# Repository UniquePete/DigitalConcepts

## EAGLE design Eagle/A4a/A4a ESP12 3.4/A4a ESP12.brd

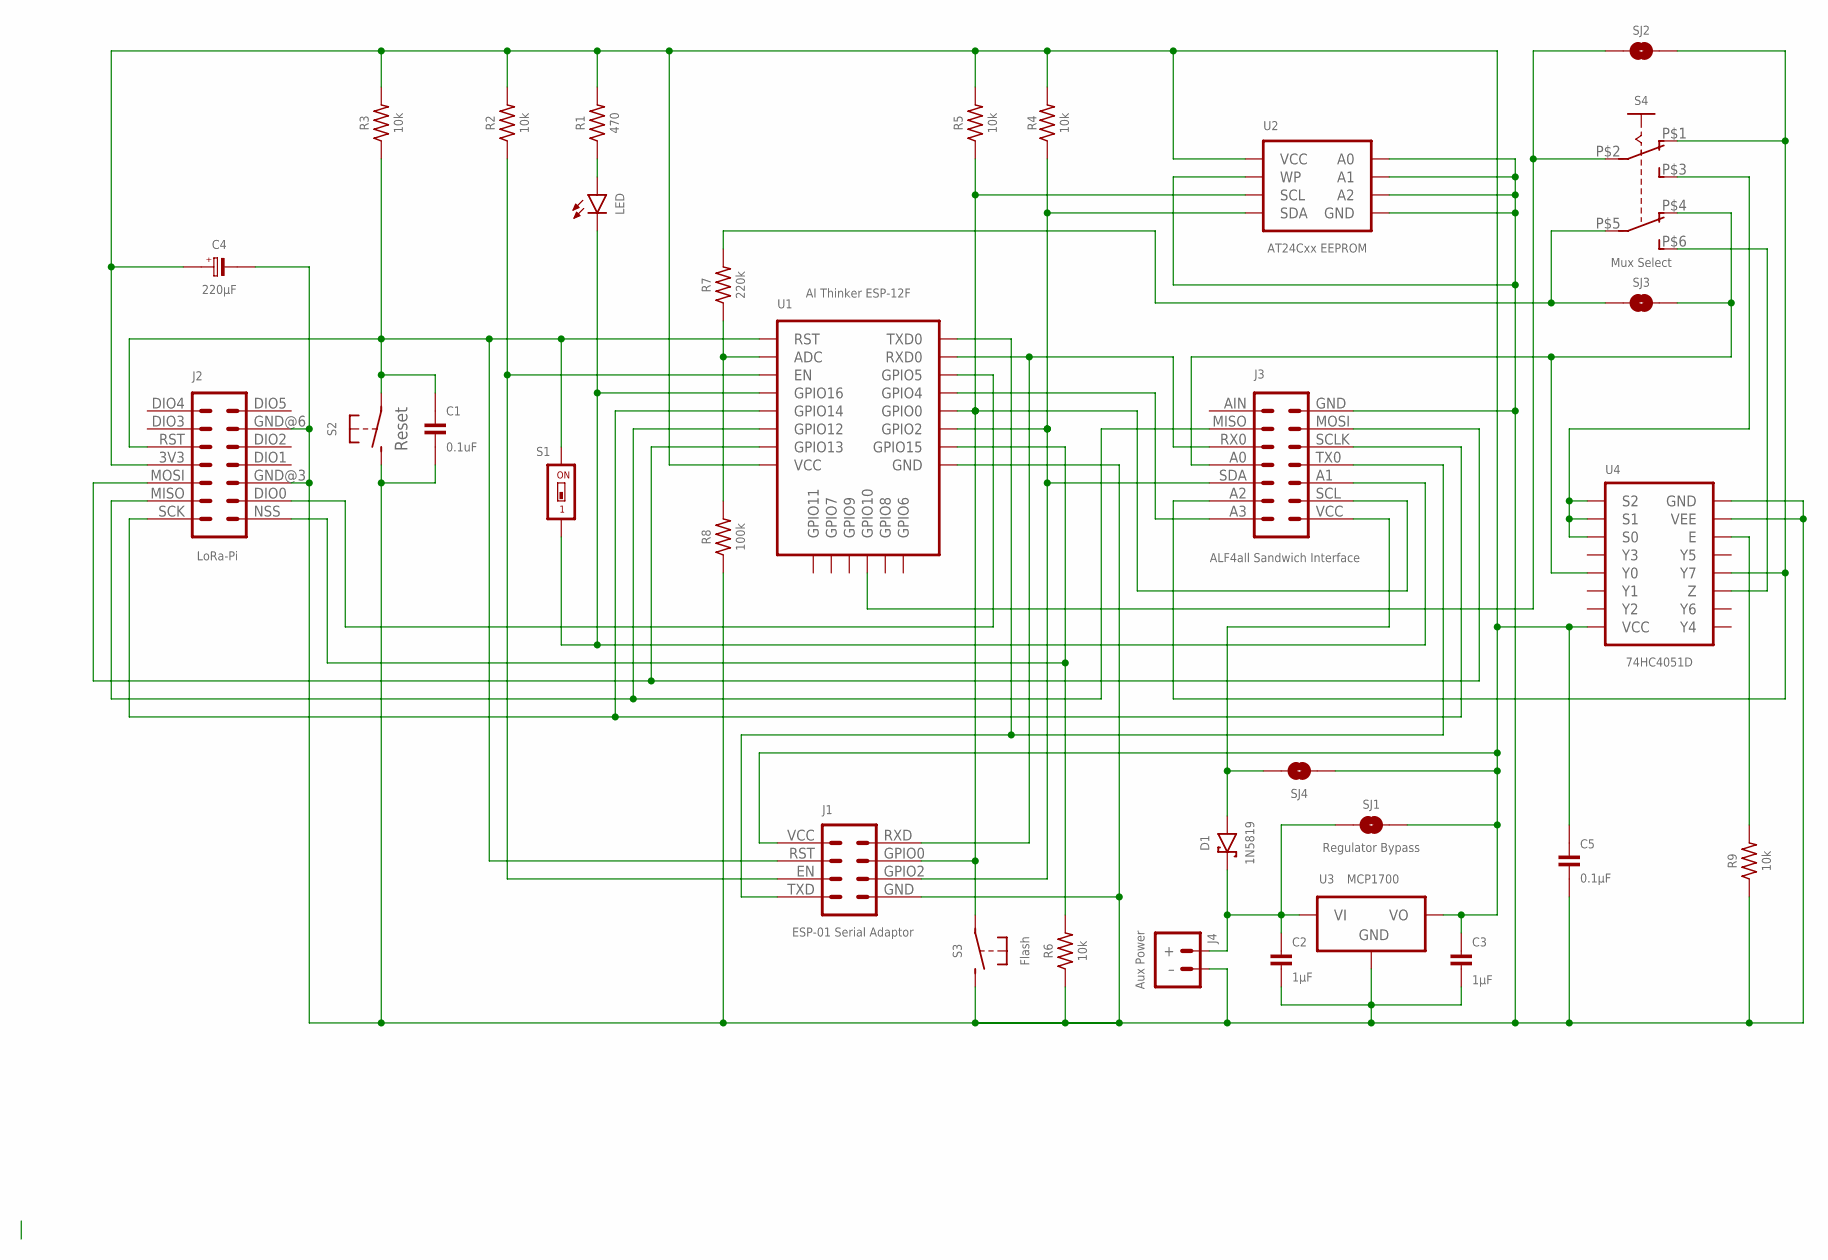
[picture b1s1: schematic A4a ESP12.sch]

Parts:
C1: 0.1uF; C0805
C2, C3: 1µF; C0805@1
C4: 220µF; C3528-21
C5: 0.1µF; C0805
D1: 1N5819; SOD-123
J1: ESP-01 Serial Adaptor; CONN_2X4-ESP-01-SERIAL
J2: LoRa-Pi; RFM95W-PI
J3: ALF4all Sandwich Interface; CONN_2X7-ALF4ALL-PROCESSOR-B
J4: Aux Power; JST-PH2.0-2-HORIZONTAL
LED: LEDCHIP-LED0805; CHIP-LED0805
R1: 470; R0805
R2, R3, R4, R5, R6, R9: 10k; R0805
R7: 220k; R0805
R8: 100k; R0805
S1: Wake; SMD-001
S2: Reset; SWITCH-2-PAD
S3: Flash; SWITCH-2-PAD
S4: Mux Select; SWITCH-DPDT-SMD
SJ1: Regulator Bypass; SJ
SJ2, SJ3, SJ4: SJ
U1: AI Thinker ESP-12F; ESP-12E/F
U2: AT24Cxx EEPROM; SOP-8
U3: MCP1700; SOT-23-3
U4: 74HC4051D; SOP16

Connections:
GND: C1.2, C2.2, C3.2, C4.2 (-), C5.2, J1.GND (1), J2.GND@3 (3), J2.GND@6 (6), J3.GND (7), J4.- (–), R6.1, R8.1, R9.1, S2.P$2 (S), S3.P$2 (S), U1.GND, U2.P$1 (A0), U2.P$2 (A1), U2.P$3 (A2), U2.P$4 (GND), U2.P$7 (WP), U3.1 (GND), U4.7 (VEE), U4.8 (GND)
unnamed: S4.P$2 (P1), SJ2.1, U1.GPIO10
unnamed: J2.NSS (1), R6.2, U1.GPIO15
unnamed: J2.SCK (14), J3.SCLK (5), U1.GPIO14
unnamed: C1.1, J1.RST (6), J2.RST (10), R3.1, S1.2, S2.P$1, U1.RST
unnamed: J2.MISO (13), J3.MISO (9), U1.GPIO12
unnamed: J2.MOSI (12), J3.MOSI (6), U1.GPIO13
unnamed: R7.1, R8.2, U1.ADC
unnamed: J1.EN (7), R2.1, U1.EN
unnamed: D1.A, J3.VCC (1), SJ4.1
unnamed: J1.TXD (8), J3.TX0 (4), U1.TXD0
unnamed: J1.GPIO2 (2), J3.SDA (12), R4.1, U1.GPIO2, U2.P$5 (SDA)
unnamed: J3.A3 (14), U1.GPIO4
unnamed: J1.GPIO0 (3), J3.SCL (2), R5.1, S3.P$1, U1.GPIO0, U2.P$6 (SCL)
unnamed: LED.A, R1.1
unnamed: J3.A1 (3), LED.C, S1.1, U1.GPIO16
unnamed: J1.RXD (4), J3.RX0 (10), U1.RXD0
unnamed: R9.2, U4.6 (E)
unnamed: J2.DIO0 (2), U1.GPIO5
unnamed: J3.A2 (13), S4.P$1 (O1), SJ2.2, U4.4 (Y7)
unnamed: J3.A0 (11), S4.P$4 (O2), SJ3.2, U4.13 (Y0)
unnamed: S4.P$6 (S2), U4.3 (Z)
unnamed: S4.P$3 (S1), U4.9 (S2), U4.10 (S1), U4.11 (S0)
unnamed: R7.2, S4.P$5 (P2), SJ3.1
unnamed: C2.1, D1.C, J4.+, SJ1.1, U3.3 (VI)
VCC: C3.1, C4.1 (+), C5.1, J1.VCC (5), J2.3V3 (11), R1.2, R2.2, R3.2, R4.2, R5.2, SJ1.2, SJ4.2, U1.VCC, U2.P$8 (VCC), U3.2 (VO), U4.16 (VCC)

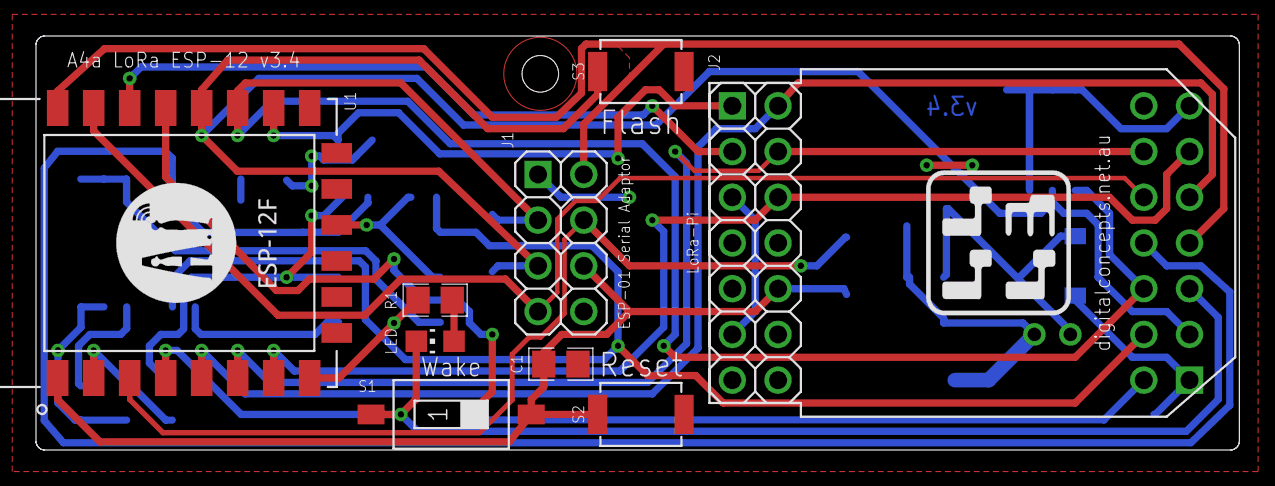
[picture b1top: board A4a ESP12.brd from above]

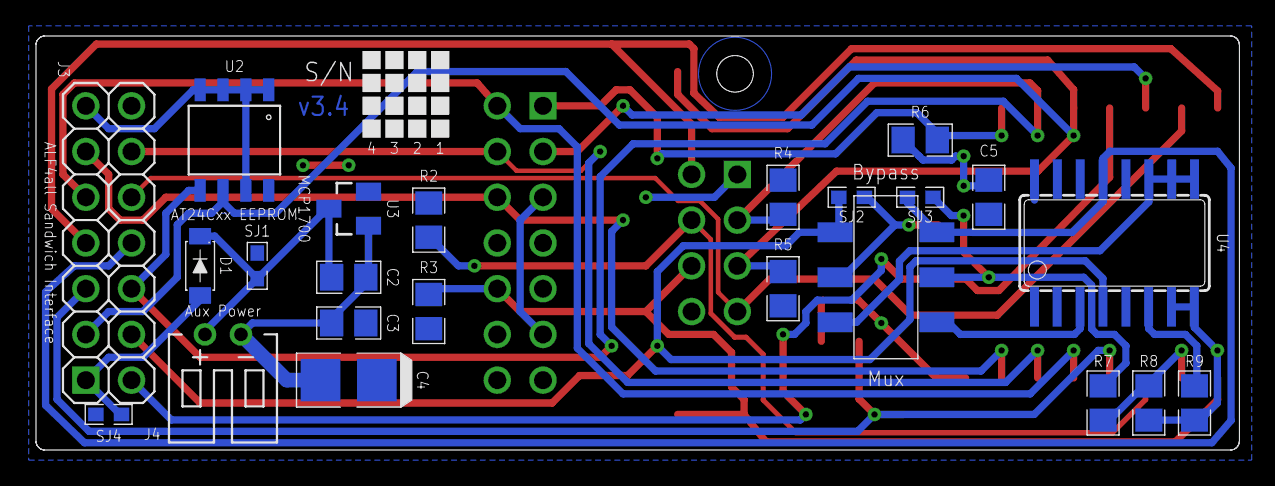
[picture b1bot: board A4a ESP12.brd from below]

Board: 2 copper layers, 66.9 x 23.0 mm, 32 parts (22 on the bottom side), 26 nets.

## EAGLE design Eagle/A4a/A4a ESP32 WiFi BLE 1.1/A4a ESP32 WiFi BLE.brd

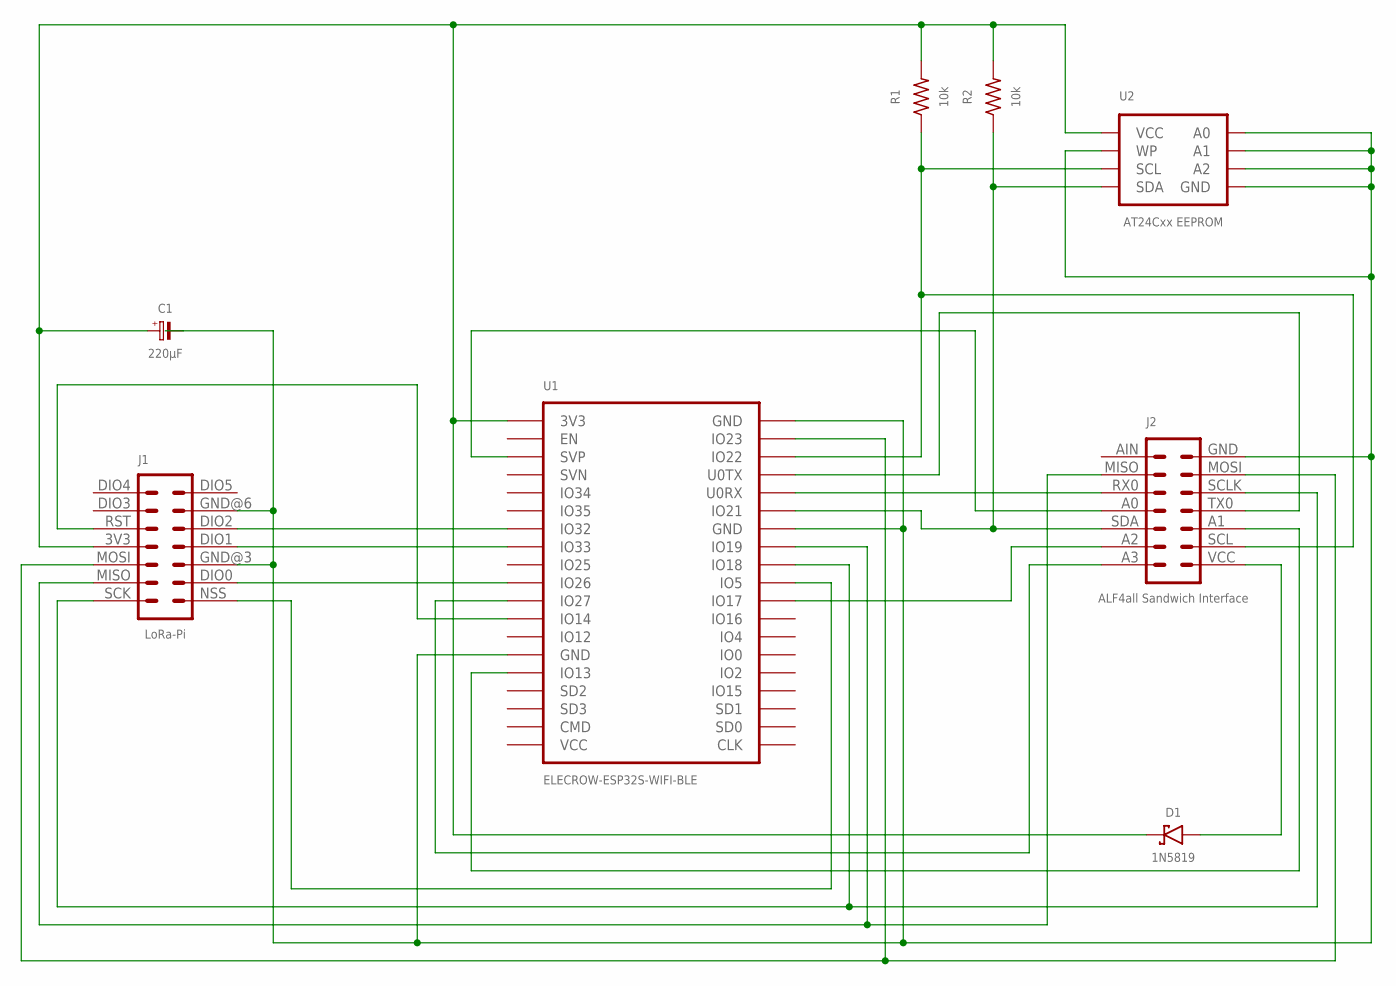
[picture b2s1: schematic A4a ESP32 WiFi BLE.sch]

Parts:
C1: 220µF; C3528-21
D1: 1N5819; SOD-123
J1: LoRa-Pi; RFM95W-PI
J2: ALF4all Sandwich Interface; CONN_2X7-ALF4ALL-PROCESSOR-B
R1, R2: 10k; R0805
U1: ELECROW-ESP32S-WIFI-BLE
U2: AT24Cxx EEPROM; SOP-8

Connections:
GND: C1.2 (-), J1.GND@3 (3), J1.GND@6 (6), J2.GND (7), U1.GND@13 (GND), U1.GND@19 (GND), U1.GND@33 (GND), U2.P$1 (A0), U2.P$2 (A1), U2.P$3 (A2), U2.P$4 (GND), U2.P$7 (WP)
unnamed: J2.A3 (14), U1.IO27
unnamed: J2.A1 (3), U1.IO13
unnamed: J1.RST (10), U1.IO14
unnamed: D1.A, J2.VCC (1)
unnamed: J1.SCK (14), J2.SCLK (5), U1.IO18
unnamed: J2.RX0 (10), U1.U0RX
unnamed: J1.DIO0 (2), U1.IO26
unnamed: J2.SDA (12), R2.1, U1.IO21, U2.P$5 (SDA)
unnamed: J2.SCL (2), R1.1, U1.IO22, U2.P$6 (SCL)
unnamed: J1.MISO (13), J2.MISO (9), U1.IO19
unnamed: J1.MOSI (12), J2.MOSI (6), U1.IO23
unnamed: J2.TX0 (4), U1.U0TX
unnamed: J1.NSS (1), U1.IO5
unnamed: J2.A2 (13), U1.IO17
unnamed: J1.DIO1 (4), U1.IO33
unnamed: J1.DIO2 (5), U1.IO32
unnamed: J2.A0 (11), U1.SVP
VCC: C1.1 (+), D1.C, J1.3V3 (11), R1.2, R2.2, U1.3V3, U2.P$8 (VCC)

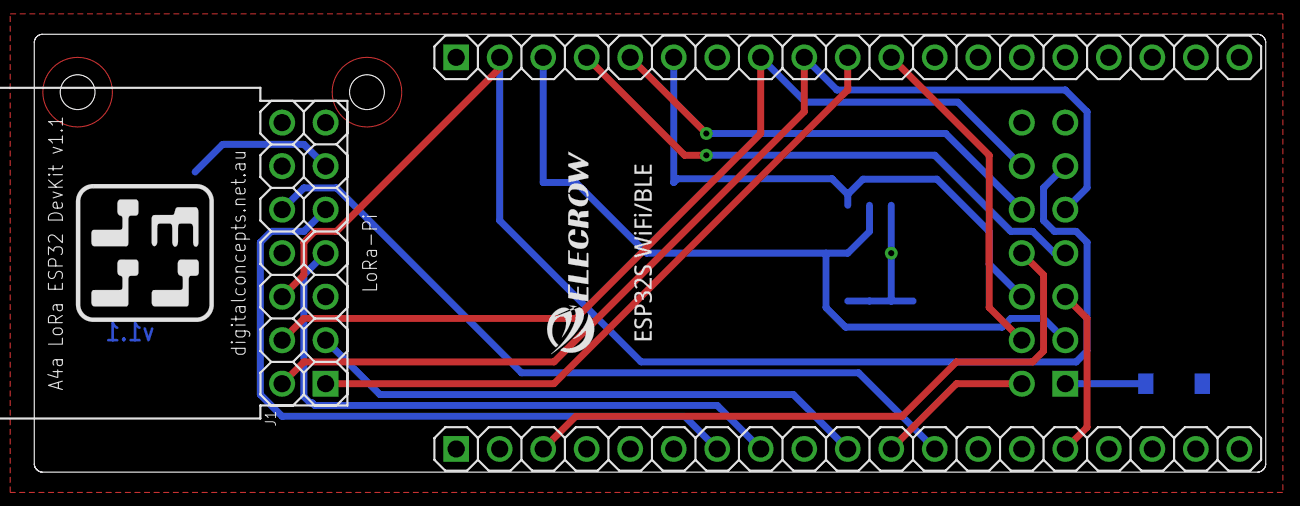
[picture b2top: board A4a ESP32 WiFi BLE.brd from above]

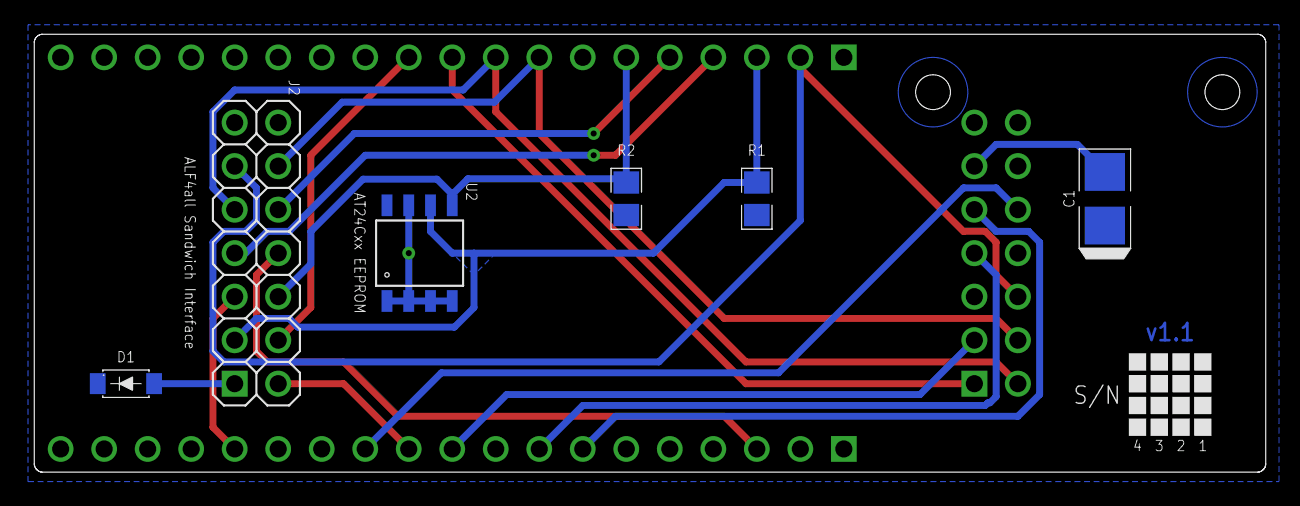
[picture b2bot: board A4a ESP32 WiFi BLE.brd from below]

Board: 2 copper layers, 71.9 x 25.6 mm, 8 parts (5 on the bottom side), 19 nets.

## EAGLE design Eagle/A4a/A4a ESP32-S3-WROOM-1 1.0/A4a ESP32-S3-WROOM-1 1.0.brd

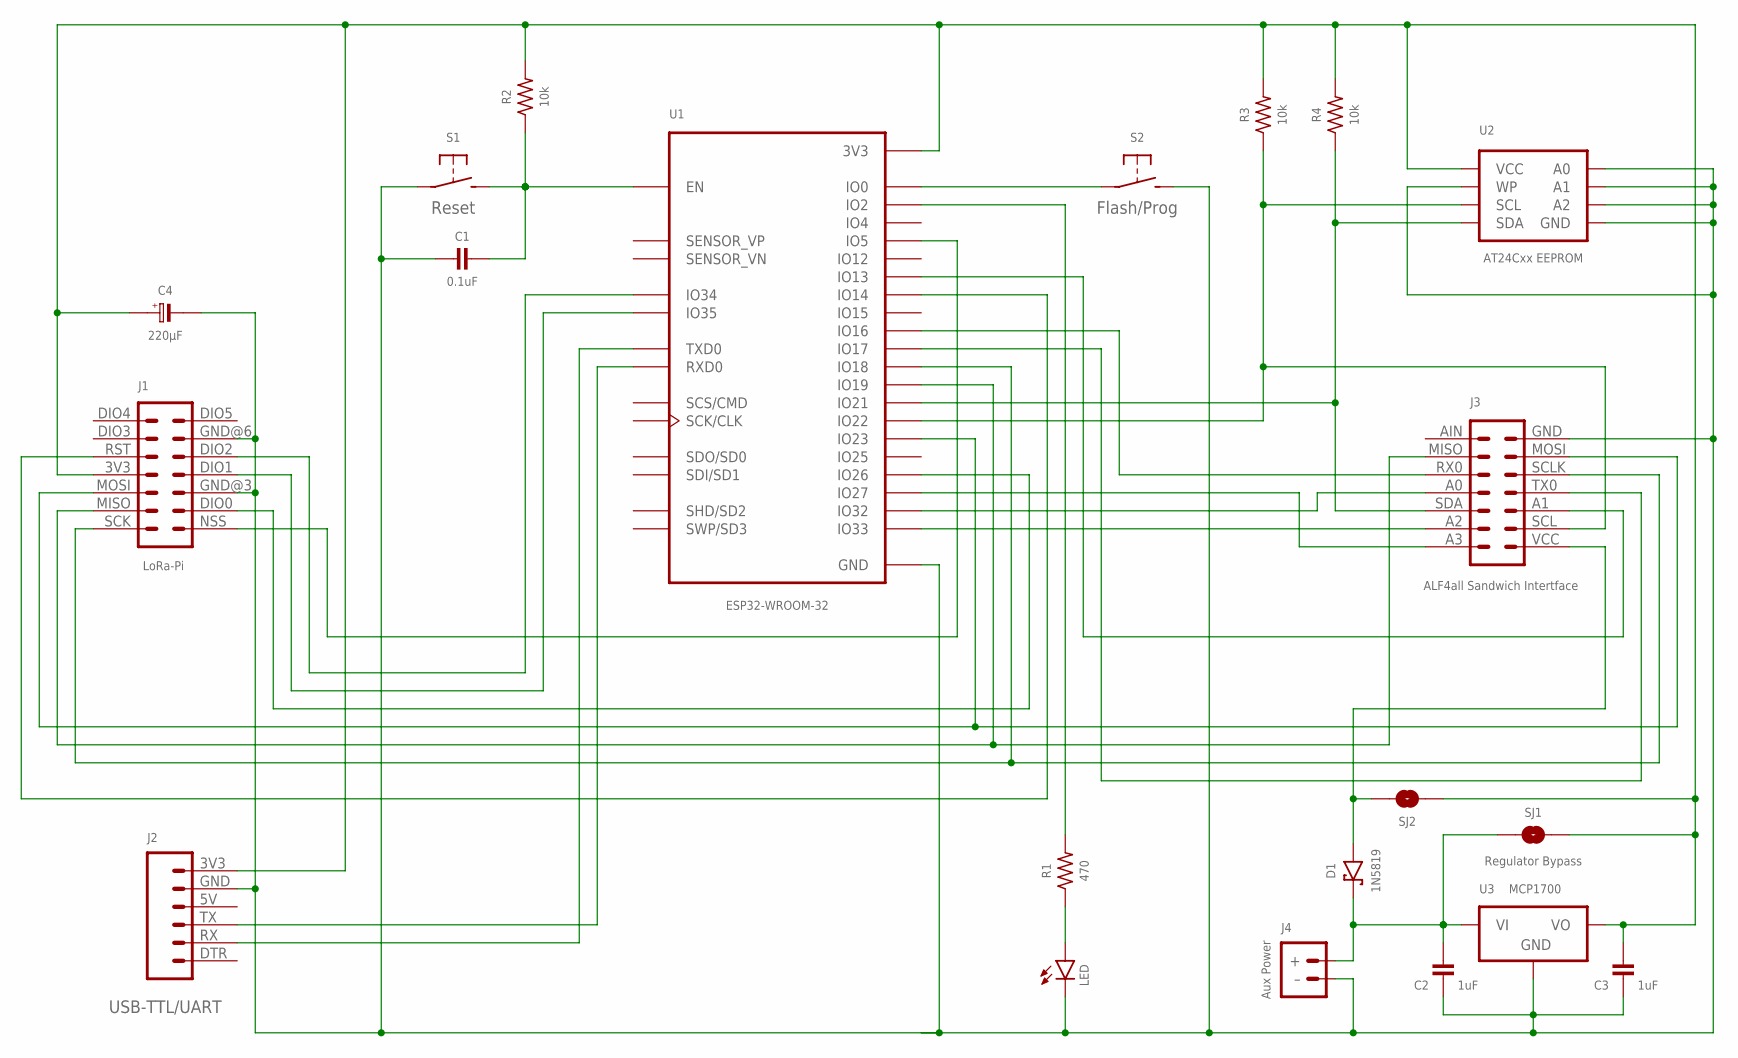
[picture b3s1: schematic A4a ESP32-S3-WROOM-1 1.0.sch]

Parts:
C1: 0.1uF; C0805@1
C2, C3: 1uF; C0805@1
C4: 220µF; C3528-21
D1: 1N5819; SOD-123
J1: LoRa-Pi; RFM95W-PI
J2: USB-TTL/UART; CONN_06-UART
J3: ALF4all Sandwich Intertface; CONN_2X7-ALF4ALL-PROCESSOR-B
J4: Aux Power; JST-PH2.0-2-HORIZONTAL
LED: LEDCHIP-LED0805; CHIP-LED0805
R1: 470; R0805
R2, R3, R4: 10k; R0805
S1: Reset; SWITCH-2-PAD
S2: Flash/Prog; SWITCH-2-PAD
SJ1: Regulator Bypass; SJ
SJ2: SJ
U1: ESP32-WROOM-32
U2: AT24Cxx EEPROM; SOP-8
U3: MCP1700; SOT-23-3

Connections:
GND: C1.2, C2.2, C3.2, C4.2 (-), J1.GND@3 (3), J1.GND@6 (6), J2.GND (5), J3.GND (7), J4.- (–), LED.C, S1.P$1, S2.P$2 (S), U1.GND@1 (GND), U1.GND@15 (GND), U1.GND@38 (GND), U1.TP (GND), U1.TP@P1 (GND), U1.TP@P2 (GND), U1.TP@P3 (GND), U1.TP@P4 (GND), U1.TP@P5 (GND), U1.TP@P6 (GND), U1.TP@P7 (GND), U1.TP@P8 (GND), U1.TP@P9 (GND), U1.TP@V1 (GND), U1.TP@V2 (GND), U1.TP@V3 (GND), U1.TP@V4 (GND), U1.TP@V5 (GND), U1.TP@V6 (GND), U1.TP@V7 (GND), U1.TP@V8 (GND), U1.TP@V9 (GND), U1.TP@V10 (GND), U1.TP@V11 (GND), U1.TP@V12 (GND), U1.TP@VP5 (GND), U2.P$1 (A0), U2.P$2 (A1), U2.P$3 (A2), U2.P$4 (GND), U2.P$7 (WP), U3.1 (GND)
unnamed: J1.DIO2 (5), U1.IO34
unnamed: J1.NSS (1), U1.IO5
unnamed: J1.SCK (14), J3.SCLK (5), U1.IO18
unnamed: J1.RST (10), U1.IO14
unnamed: J1.MISO (13), J3.MISO (9), U1.IO19
unnamed: J1.MOSI (12), J3.MOSI (6), U1.IO23
unnamed: LED.A, R1.1
unnamed: S2.P$1, U1.IO0
unnamed: J3.RX0 (10), U1.IO16
unnamed: C2.1, D1.C, J4.+, SJ1.1, U3.3 (VI)
unnamed: D1.A, J3.VCC (1), SJ2.1
unnamed: J3.SCL (2), R3.1, U1.IO22, U2.P$6 (SCL)
unnamed: C1.1, R2.1, S1.P$2 (S), U1.EN
unnamed: J3.SDA (12), R4.1, U1.IO21, U2.P$5 (SDA)
unnamed: J3.A1 (3), U1.IO13
unnamed: J2.TX (3), U1.RXD0
unnamed: R1.2, U1.IO2
unnamed: J1.DIO0 (2), U1.IO26
unnamed: J3.A2 (13), U1.IO33
unnamed: J2.RX (2), U1.TXD0
unnamed: J3.A0 (11), U1.IO32
unnamed: J3.A3 (14), U1.IO27
unnamed: J1.DIO1 (4), U1.IO35
VC: J3.TX0 (4), U1.IO17
VCC: C3.1, C4.1 (+), J1.3V3 (11), J2.3V3 (6), R2.2, R3.2, R4.2, SJ1.2, SJ2.2, U1.3V3, U2.P$8 (VCC), U3.2 (VO)

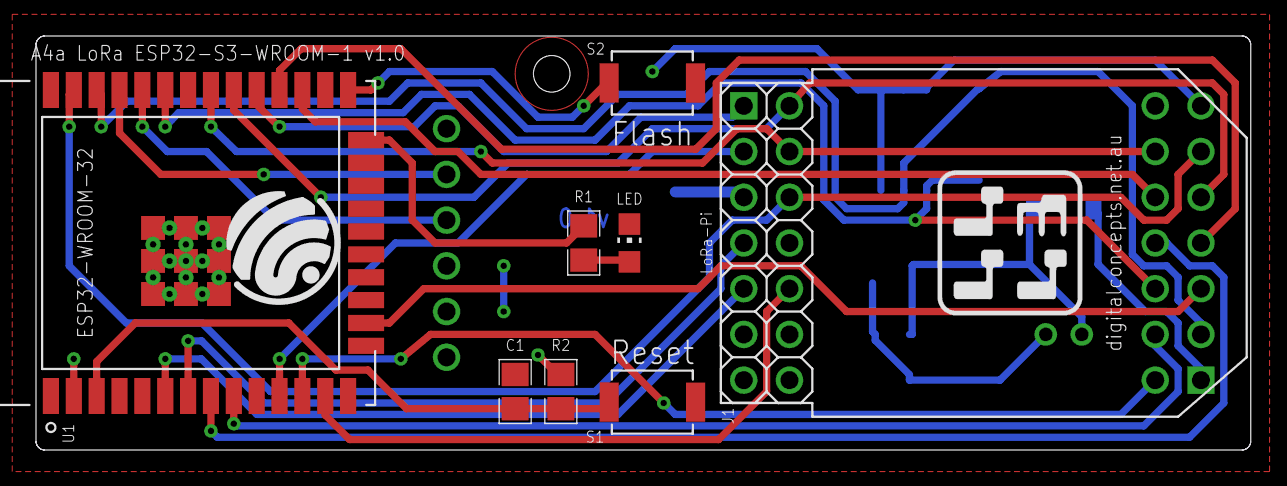
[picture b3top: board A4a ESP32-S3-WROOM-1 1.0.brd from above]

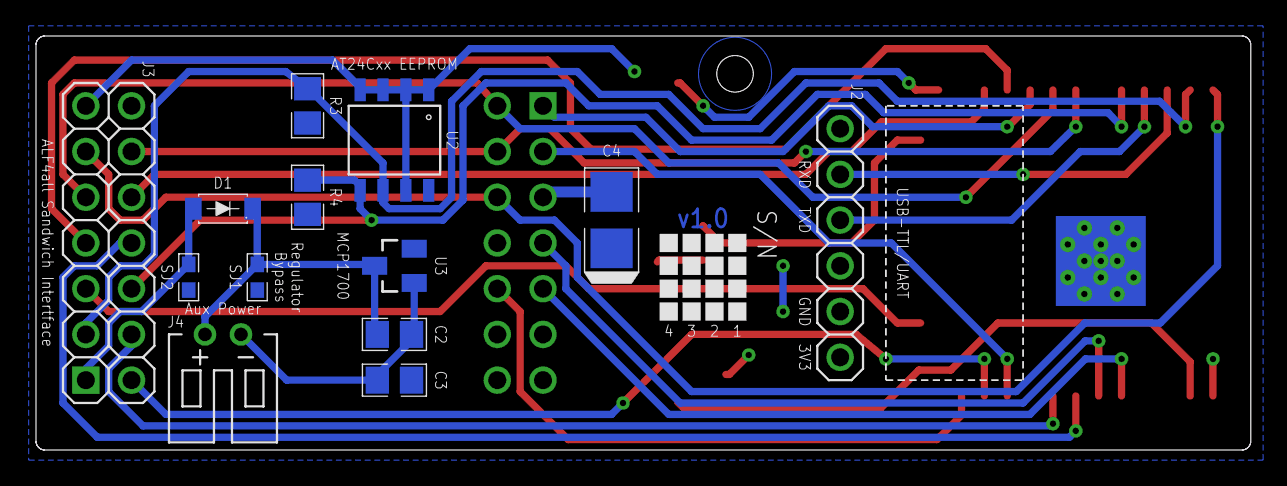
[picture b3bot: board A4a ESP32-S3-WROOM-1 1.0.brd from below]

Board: 2 copper layers, 67.5 x 23.0 mm, 21 parts (12 on the bottom side), 26 nets.

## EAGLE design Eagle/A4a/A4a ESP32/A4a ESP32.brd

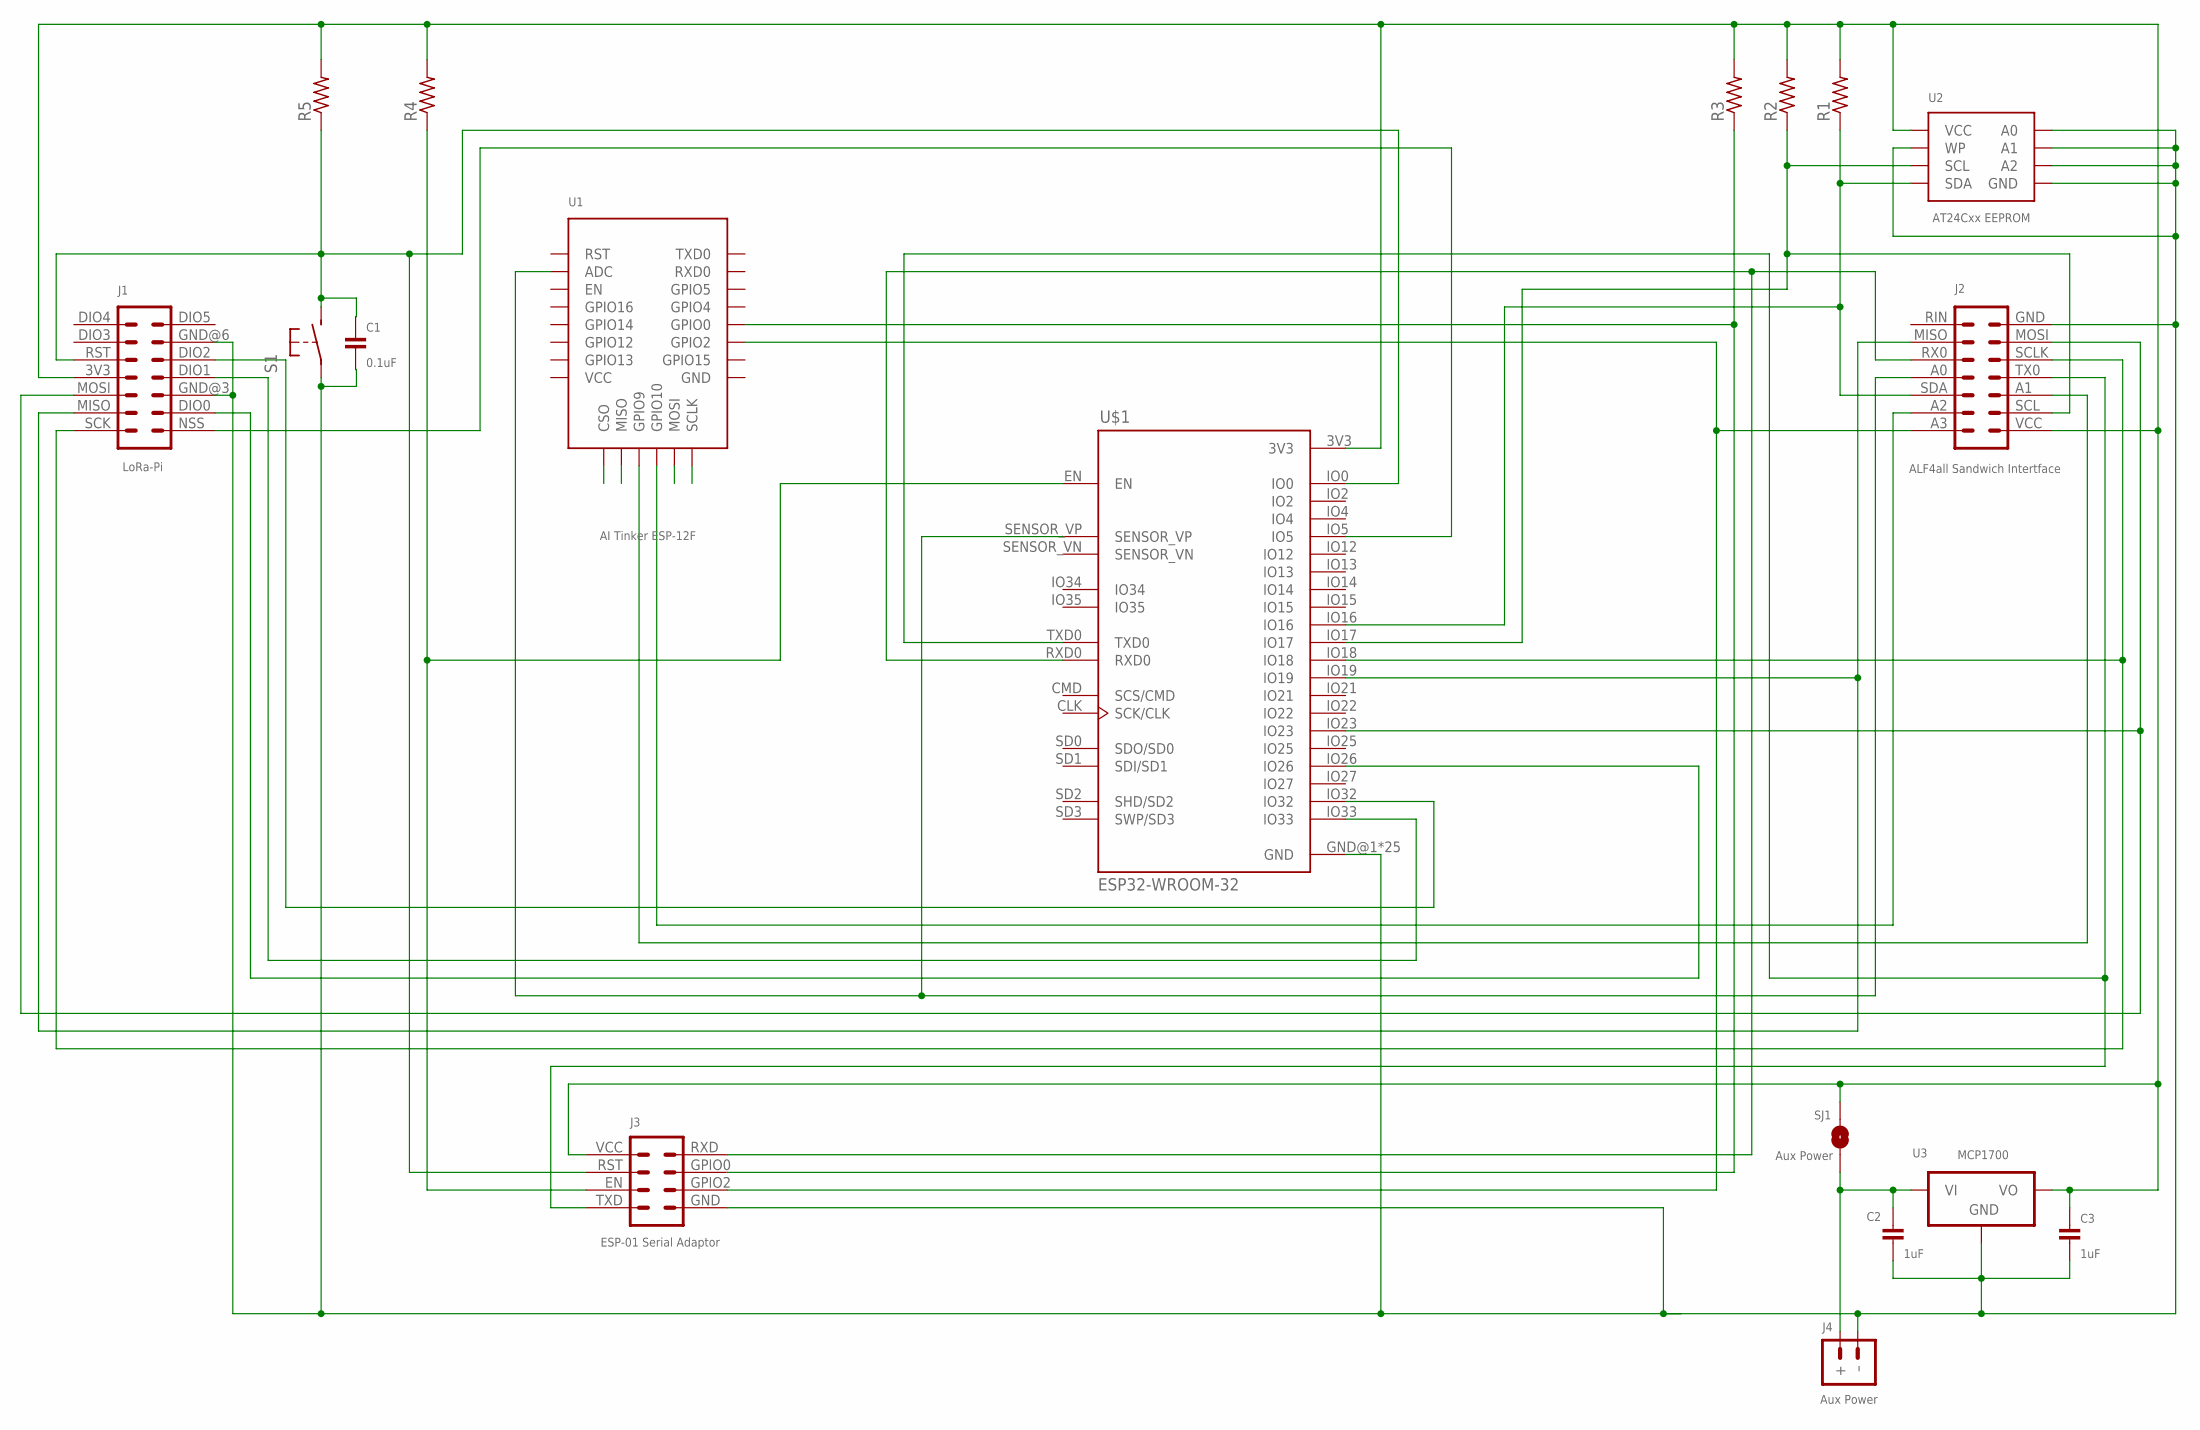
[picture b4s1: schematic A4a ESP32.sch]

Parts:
C1: 0.1uF; C0805
C2, C3: 1uF; C0805
J1: LoRa-Pi; RFM95W-PI
J2: ALF4all Sandwich Intertface; CONN_2X7-ALF4ALL-PROCESSOR-B
J3: ESP-01 Serial Adaptor; CONN_2X4-ESP-01-SERIAL
J4: Aux Power; JST-PH2.0-2-HORIZONTAL
R1: RESISTOR-VIA-1; R0805-VIA-1
R2, R3, R4, R5: RESISTORR0805; R0805
S1: SWITCH-MOMENTARY-2-PIN; SWITCH-2-PAD
SJ1: Aux Power; SJ
U1: AI Tinker ESP-12F; ESP-12E/F-WITH-VIAS
U2: AT24Cxx EEPROM; SOP-8-WITH-VIA-7
U3: MCP1700; SOT-23-3-VIA-GND
U$1: ESP32-WROOM-32

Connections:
GND: C1.2, C2.2, C3.2, J1.GND@3 (3), J1.GND@6 (6), J2.GND (7), J3.GND (1), J4.- (–), S1.P$1, U2.P$1 (A0), U2.P$2 (A1), U2.P$3 (A2), U2.P$4 (GND), U2.P$7 (WP), U2.P$7@VIA (WP), U3.GND, U3.GND@VIA (GND), U$1.GND@1 (GND), U$1.GND@15 (GND), U$1.GND@38 (GND), U$1.TP (GND), U$1.TP@P1 (GND), U$1.TP@P2 (GND), U$1.TP@P3 (GND), U$1.TP@P4 (GND), U$1.TP@P5 (GND), U$1.TP@P6 (GND), U$1.TP@P7 (GND), U$1.TP@P8 (GND), U$1.TP@P9 (GND), U$1.TP@V1 (GND), U$1.TP@V2 (GND), U$1.TP@V3 (GND), U$1.TP@V4 (GND), U$1.TP@V5 (GND), U$1.TP@V6 (GND), U$1.TP@V7 (GND), U$1.TP@V8 (GND), U$1.TP@V9 (GND), U$1.TP@V10 (GND), U$1.TP@V11 (GND), U$1.TP@V12 (GND)
unnamed: U1.CS0 (CSO), U1.CS0@VIA (CSO)
unnamed: J1.NSS (1), U$1.IO5
unnamed: J1.SCK (14), J2.SCLK (5), U$1.IO18
unnamed: C1.1, J1.RST (10), J3.RST (6), R5.1, S1.P$2 (S), U$1.IO0
unnamed: J1.MISO (13), J2.MISO (9), U$1.IO19
unnamed: J1.MOSI (12), J2.MOSI (6), U$1.IO23
unnamed: U1.MISO, U1.MISO@VIA (MISO)
unnamed: J3.EN (7), R4.1, U$1.EN
unnamed: J2.A0 (11), U1.ADC, U1.ADC@VIA (ADC), U$1.SENSOR_VP
unnamed: J2.TX0 (4), J3.TXD (8), U$1.TXD0
unnamed: J2.A3 (14), J3.GPIO2 (2), U1.GPIO2, U1.GPIO2@VIA (GPIO2)
unnamed: J2.SCL (2), R2.1, U2.P$6 (SCL), U$1.IO17
unnamed: J3.GPIO0 (3), R3.1, U1.GPIO0, U1.GPIO0@VIA (GPIO0)
unnamed: J2.SDA (12), R1.1, R1.1@VIA (1), U2.P$5 (SDA), U$1.IO16
unnamed: J2.A1 (3), U1.GPIO9, U1.GPIO9@VIA (GPIO9)
unnamed: J2.RX0 (10), J3.RXD (4), U$1.RXD0
unnamed: J2.A2 (13), U1.GPIO10, U1.GPIO10@VIA (GPIO10)
unnamed: J1.DIO0 (2), U$1.IO26
unnamed: U1.MOSI, U1.MOSI@VIA (MOSI)
unnamed: U1.SCLK, U1.SCLK@VIA (SCLK)
unnamed: J1.DIO1 (4), U$1.IO33
unnamed: J1.DIO2 (5), U$1.IO32
unnamed: C2.1, J4.+, SJ1.1, U3.VIN (VI)
VCC: C3.1, J1.3V3 (11), J2.VCC (1), J3.VCC (5), R1.2, R2.2, R3.2, R4.2, R5.2, SJ1.2, U2.P$8 (VCC), U3.VOUT (VO), U$1.3V3

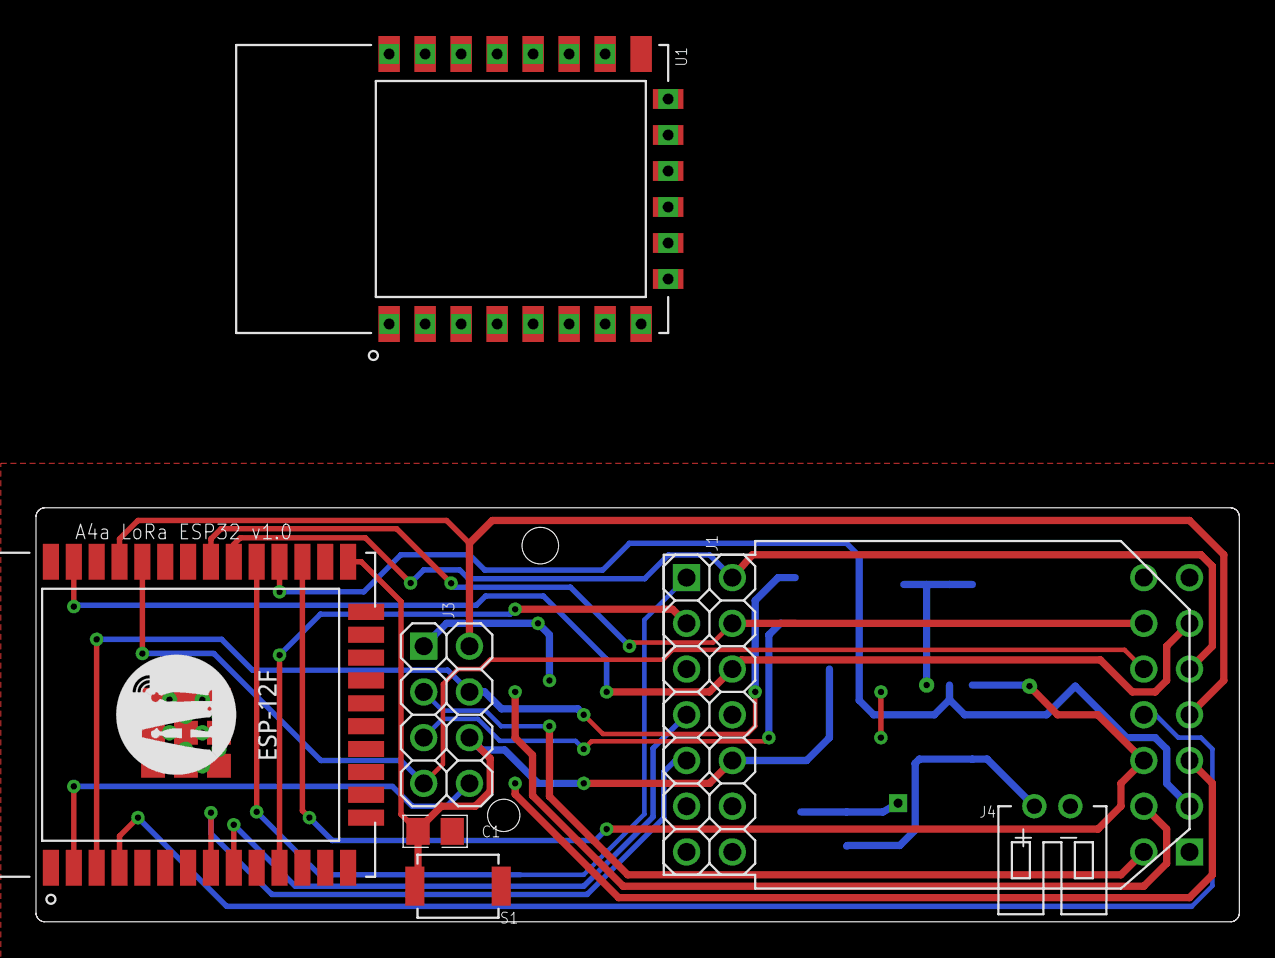
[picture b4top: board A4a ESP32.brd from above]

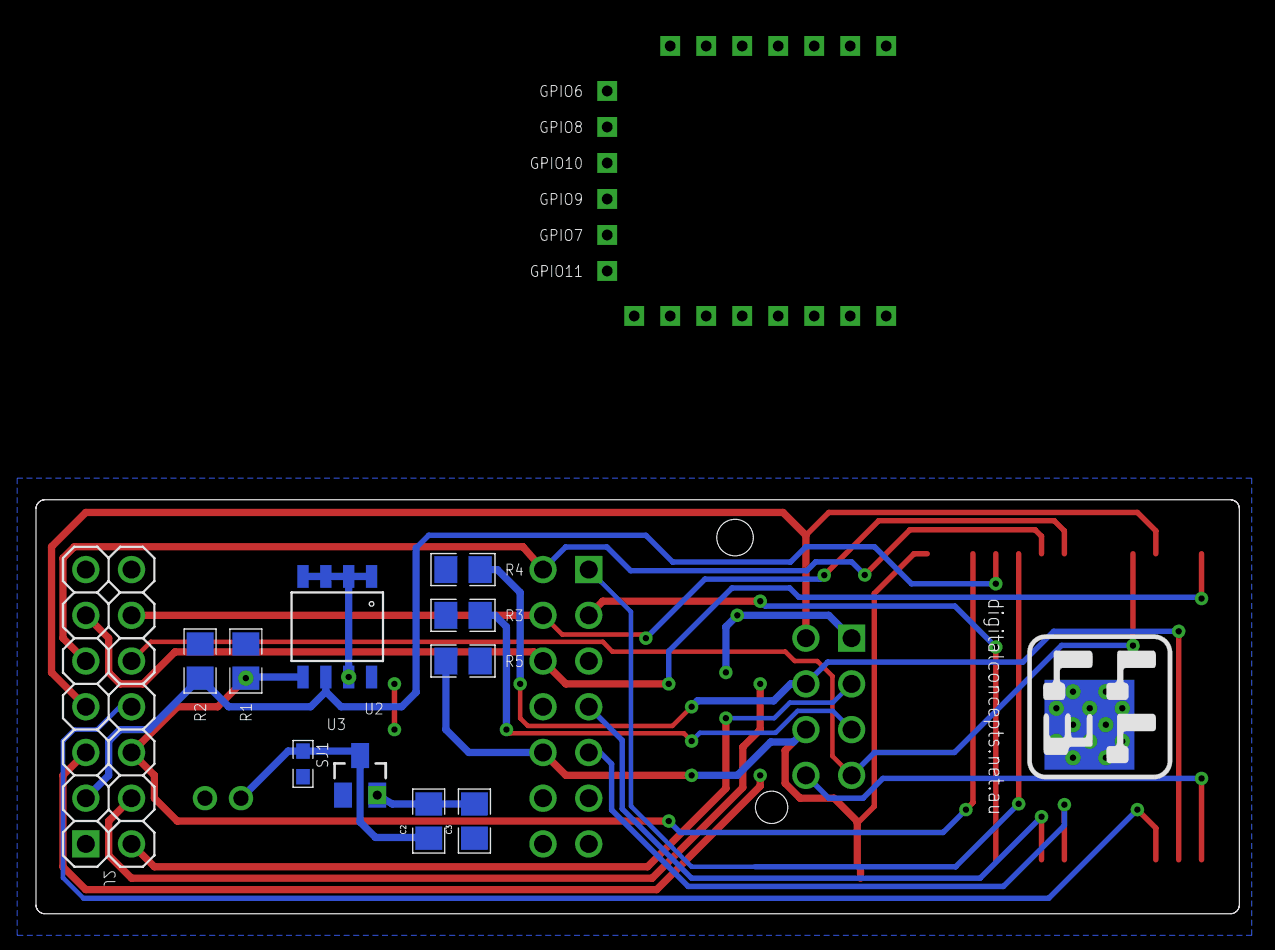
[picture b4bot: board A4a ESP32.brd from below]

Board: 2 copper layers, 66.9 x 23.0 mm, 18 parts (10 on the bottom side), 25 nets.

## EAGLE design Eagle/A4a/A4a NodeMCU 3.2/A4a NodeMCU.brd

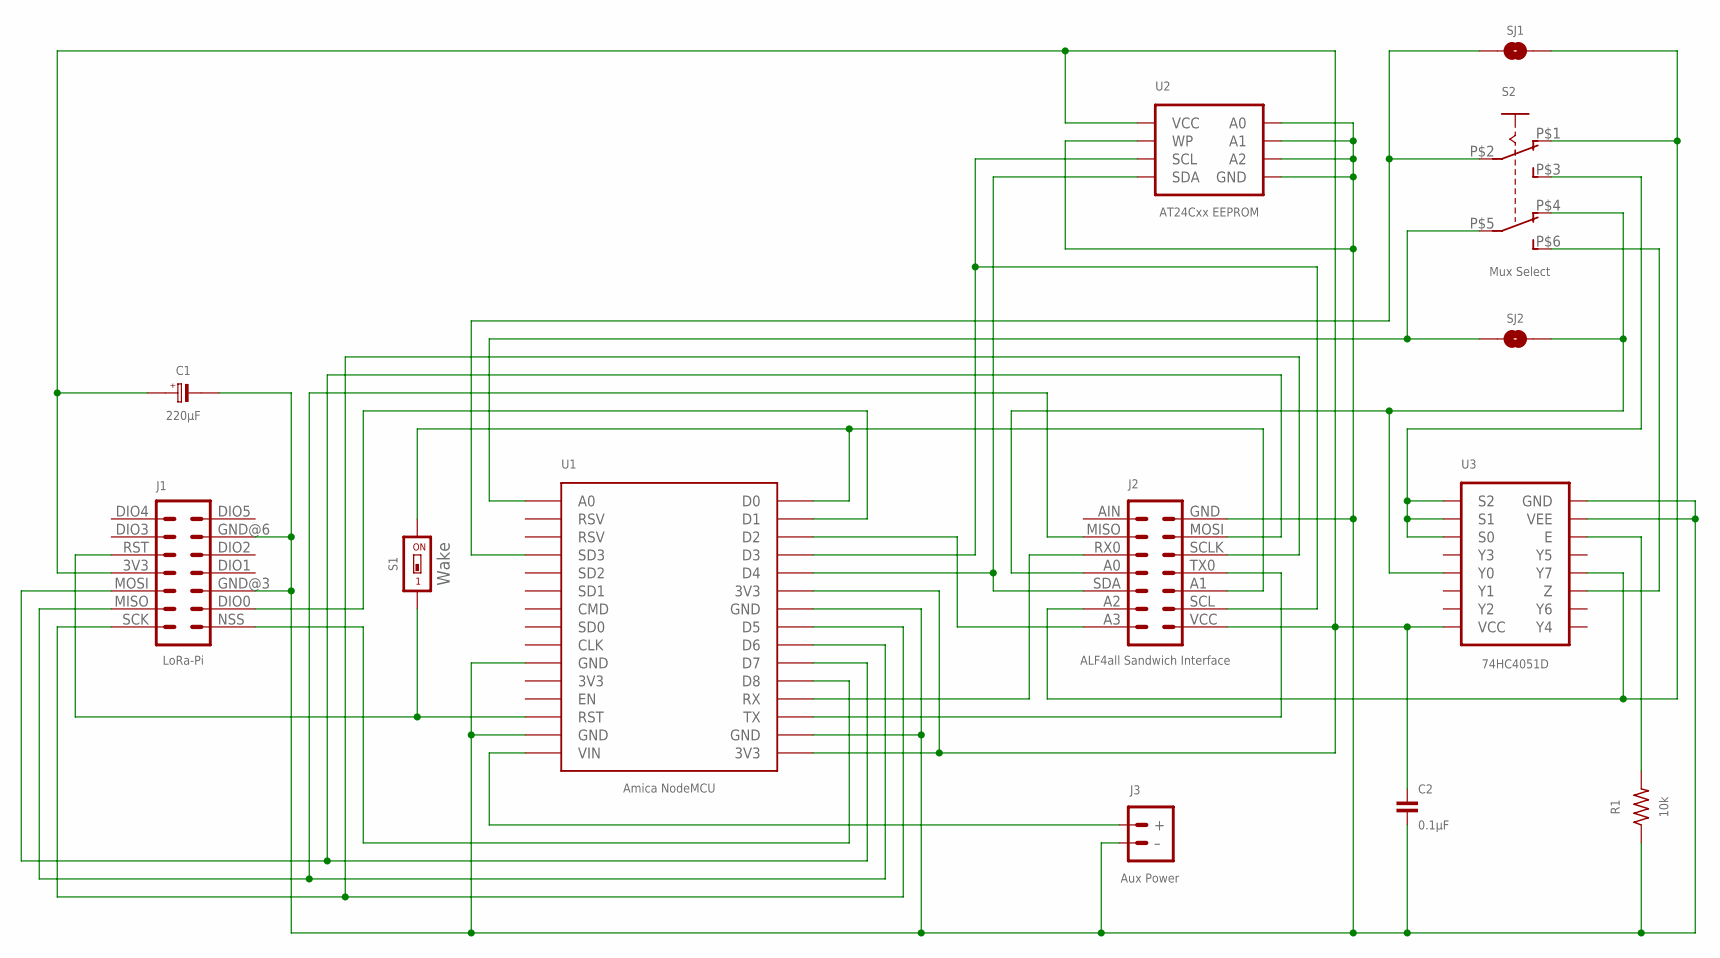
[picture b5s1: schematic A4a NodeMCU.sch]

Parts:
C1: 220µF; C3528-21
C2: 0.1µF; C0805
J1: LoRa-Pi; RFM95W-PI
J2: ALF4all Sandwich Interface; CONN_2X7-ALF4ALL-PROCESSOR-B
J3: Aux Power; JST-PH2.0-2-HORIZONTAL
R1: 10k; R0805
S1: Wake; SMD-001
S2: Mux Select; SWITCH-DPDT-SMD
SJ1, SJ2: SJ
U1: Amica NodeMCU; AMICA-NODEMCU
U2: AT24Cxx EEPROM; SOP-8
U3: 74HC4051D; SOP16

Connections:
GND: C1.2 (-), C2.2, J1.GND@3 (3), J1.GND@6 (6), J2.GND (7), J3.- (–), R1.1, U1.GND@2 (GND), U1.GND@9 (GND), U1.GND@25 (GND), U1.GND@29 (GND), U2.P$1 (A0), U2.P$2 (A1), U2.P$3 (A2), U2.P$4 (GND), U2.P$7 (WP), U3.7 (VEE), U3.8 (GND)
unnamed: S2.P$5 (P2), SJ2.1, U1.A0
unnamed: J2.A3 (14), U1.D2
unnamed: J2.A1 (3), S1.2, U1.D0
unnamed: J1.RST (10), S1.1, U1.RST
unnamed: J2.A0 (11), S2.P$4 (O2), SJ2.2, U3.13 (Y0)
unnamed: J1.SCK (14), J2.SCLK (5), U1.D5
unnamed: J2.RX0 (10), U1.RX
unnamed: R1.2, U3.6 (E)
unnamed: J3.+, U1.VIN
unnamed: J2.SDA (12), U1.D4, U2.P$5 (SDA)
unnamed: J2.SCL (2), U1.D3, U2.P$6 (SCL)
unnamed: J1.MISO (13), J2.MISO (9), U1.D6
unnamed: J1.MOSI (12), J2.MOSI (6), U1.D7
unnamed: J2.TX0 (4), U1.TX
unnamed: J1.NSS (1), U1.D8
unnamed: S2.P$3 (S1), U3.9 (S2), U3.10 (S1), U3.11 (S0)
unnamed: J1.DIO0 (2), U1.D1
unnamed: S2.P$2 (P1), SJ1.1, U1.SD3
unnamed: S2.P$6 (S2), U3.3 (Z)
unnamed: J2.A2 (13), S2.P$1 (O1), SJ1.2, U3.4 (Y7)
VCC: C1.1 (+), C2.1, J1.3V3 (11), J2.VCC (1), U1.3V3@1 (3V3), U1.3V3@10 (3V3), U2.P$8 (VCC), U3.16 (VCC)
